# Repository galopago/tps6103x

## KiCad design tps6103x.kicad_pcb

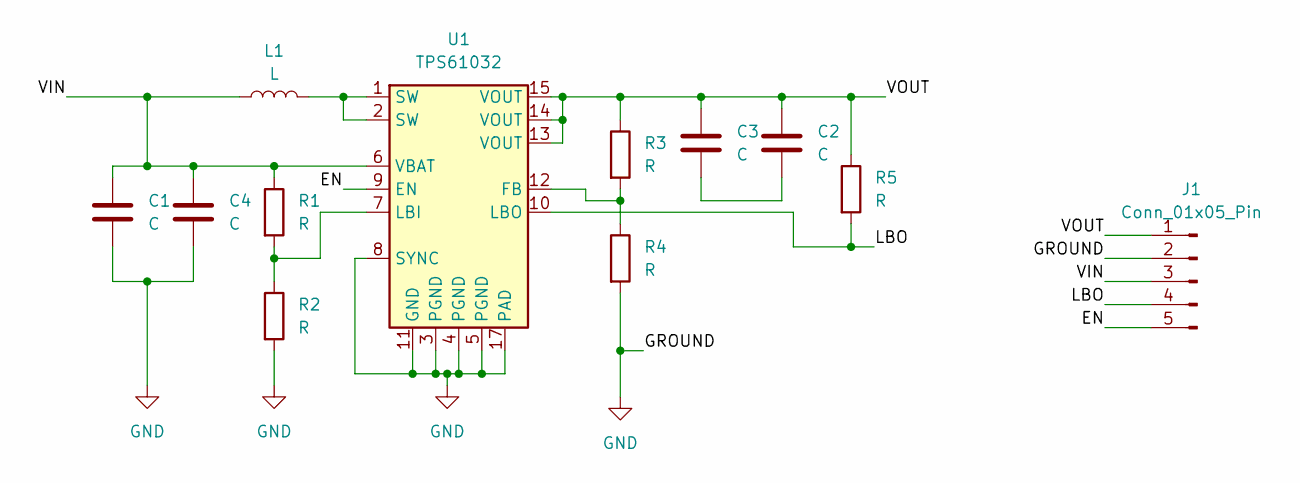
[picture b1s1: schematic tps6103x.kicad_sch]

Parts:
C1, C2: C; C_0805_2012Metric_Pad1.18x1.45mm_HandSolder
C3, C4: C; CP_Elec_8x10.5
J1: Conn_01x05_Pin; PinHeader_1x05_P2.54mm_Vertical
L1: L; L_Sumida_CDRH124_12.3x12.3mm
R1, R2, R3, R4, R5: R; R_0805_2012Metric_Pad1.20x1.40mm_HandSolder
U1: TPS61032; HTSSOP-16-1EP_4.4x5mm_P0.65mm_EP3.4x5mm

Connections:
/EN: J1.5, U1.9 (EN)
/LBO: J1.4, R5.2, U1.10 (LBO)
/VIN: C1.1, C4.1, J1.3, L1.1, R1.1, U1.6 (VBAT)
/VOUT: C2.1, C3.1, J1.1, R3.1, R5.1, U1.13 (VOUT), U1.14 (VOUT), U1.15 (VOUT)
GND: C1.2, C4.2, J1.2, R2.2, R4.2, U1.3 (PGND), U1.4 (PGND), U1.5 (PGND), U1.8 (SYNC), U1.11 (GND), U1.17 (PAD)
unnamed: C2.2, C3.2
unnamed: L1.2, U1.1 (SW), U1.2 (SW)
unnamed: R3.2, R4.1, U1.12 (FB)
unnamed: R1.2, R2.1, U1.7 (LBI)

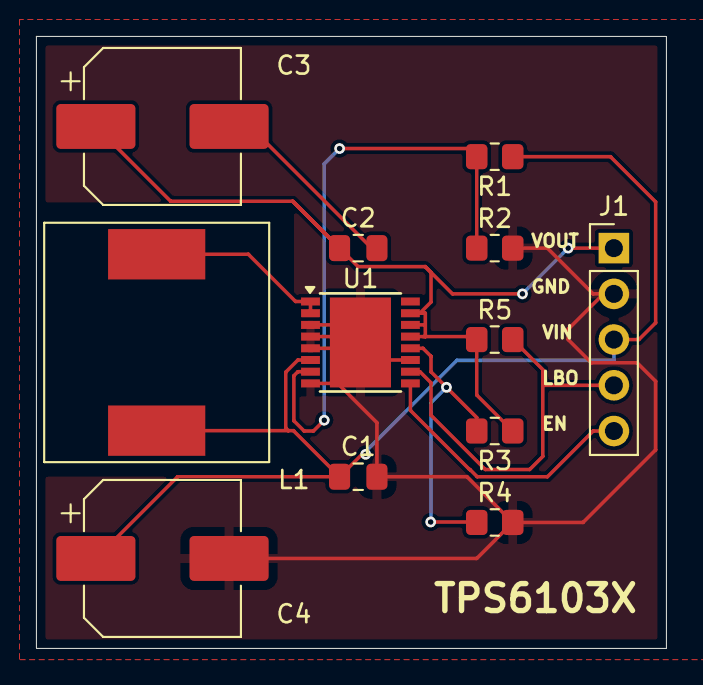
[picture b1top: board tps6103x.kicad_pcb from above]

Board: 2 copper layers, 35.0 x 34.0 mm, 12 parts (0 on the bottom side), 9 nets.

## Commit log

2026-01-17 PCB for DC boost integrated circuit tps6103x testing
2026-01-17 gerber files for single board
2026-01-17 gerber files for PCB panel
